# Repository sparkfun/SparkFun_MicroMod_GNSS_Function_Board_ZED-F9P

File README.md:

SparkFun MicroMod GNSS Function Board - ZED-F9P
========================================

[*SparkFun MicroMod GNSS Function Board - ZED-F9P (GPS-19663)*](https://www.sparkfun.com/products/19663)

The SparkFun MicroMod GNSS Function Board - ZED-F9P provides high precision GNSS capabilities for MicroMod projects using Main Board/Function Board assemblies. The ZED-F9P module from u-blox is capable of up to 10mm 3-dimensional accuracy though the module requires a clear view of the sky as well as correction data from an RTCM source to achieve this level of precision. The ZED-F9P can act as a base station as well so you can use it with a second Function Board (or another SparkFun ZED-F9P product) together to achieve millimeter positional accuracy.

Repository Contents
-------------------

* **/Documentation** - Data sheets, additional product information
* **/Firmware** - Example code 
* **/Hardware** - Eagle design files (.brd, .sch)
* **/Libraries** - Libraries for use with the <PRODUCT NAME>
* **/Production** - Production panel files (.brd)
* **/Software** - Related software for the <PRODUCT NAME>

Documentation
--------------
* **[SparkFun u-blox GNSS Arduino Library](https://github.com/sparkfun/SparkFun_u-blox_GNSS_Arduino_Library)** - u-blox GNSS Arduino library for SparkFun u-blox products.
* **[Hookup Guide](https://learn.sparkfun.com/tutorials/micromod-gnss-function-board---zed-f9p-hookup-guide)** - Basic hookup guide for the MicroMod GNSS Function Board - ZED-F9P.

Product Versions
----------------
* [GPS-19663](https://www.sparkfun.com/products/19663)- MicroMod GNSS Function Board - ZED-F9P Initial Release

Issues
------------
See the [issue template](.github/ISSUE_TEMPLATE/) folder for more information on how to raise issues for bugs and new features.

License Information
-------------------

This product is _**open source**_! 

Please review the LICENSE.md file for license information. 

If you have any questions or concerns on licensing, please contact technical support on our [SparkFun forums](https://forum.sparkfun.com/viewforum.php?f=152).

Distributed as-is; no warranty is given.

- Your friends at SparkFun.

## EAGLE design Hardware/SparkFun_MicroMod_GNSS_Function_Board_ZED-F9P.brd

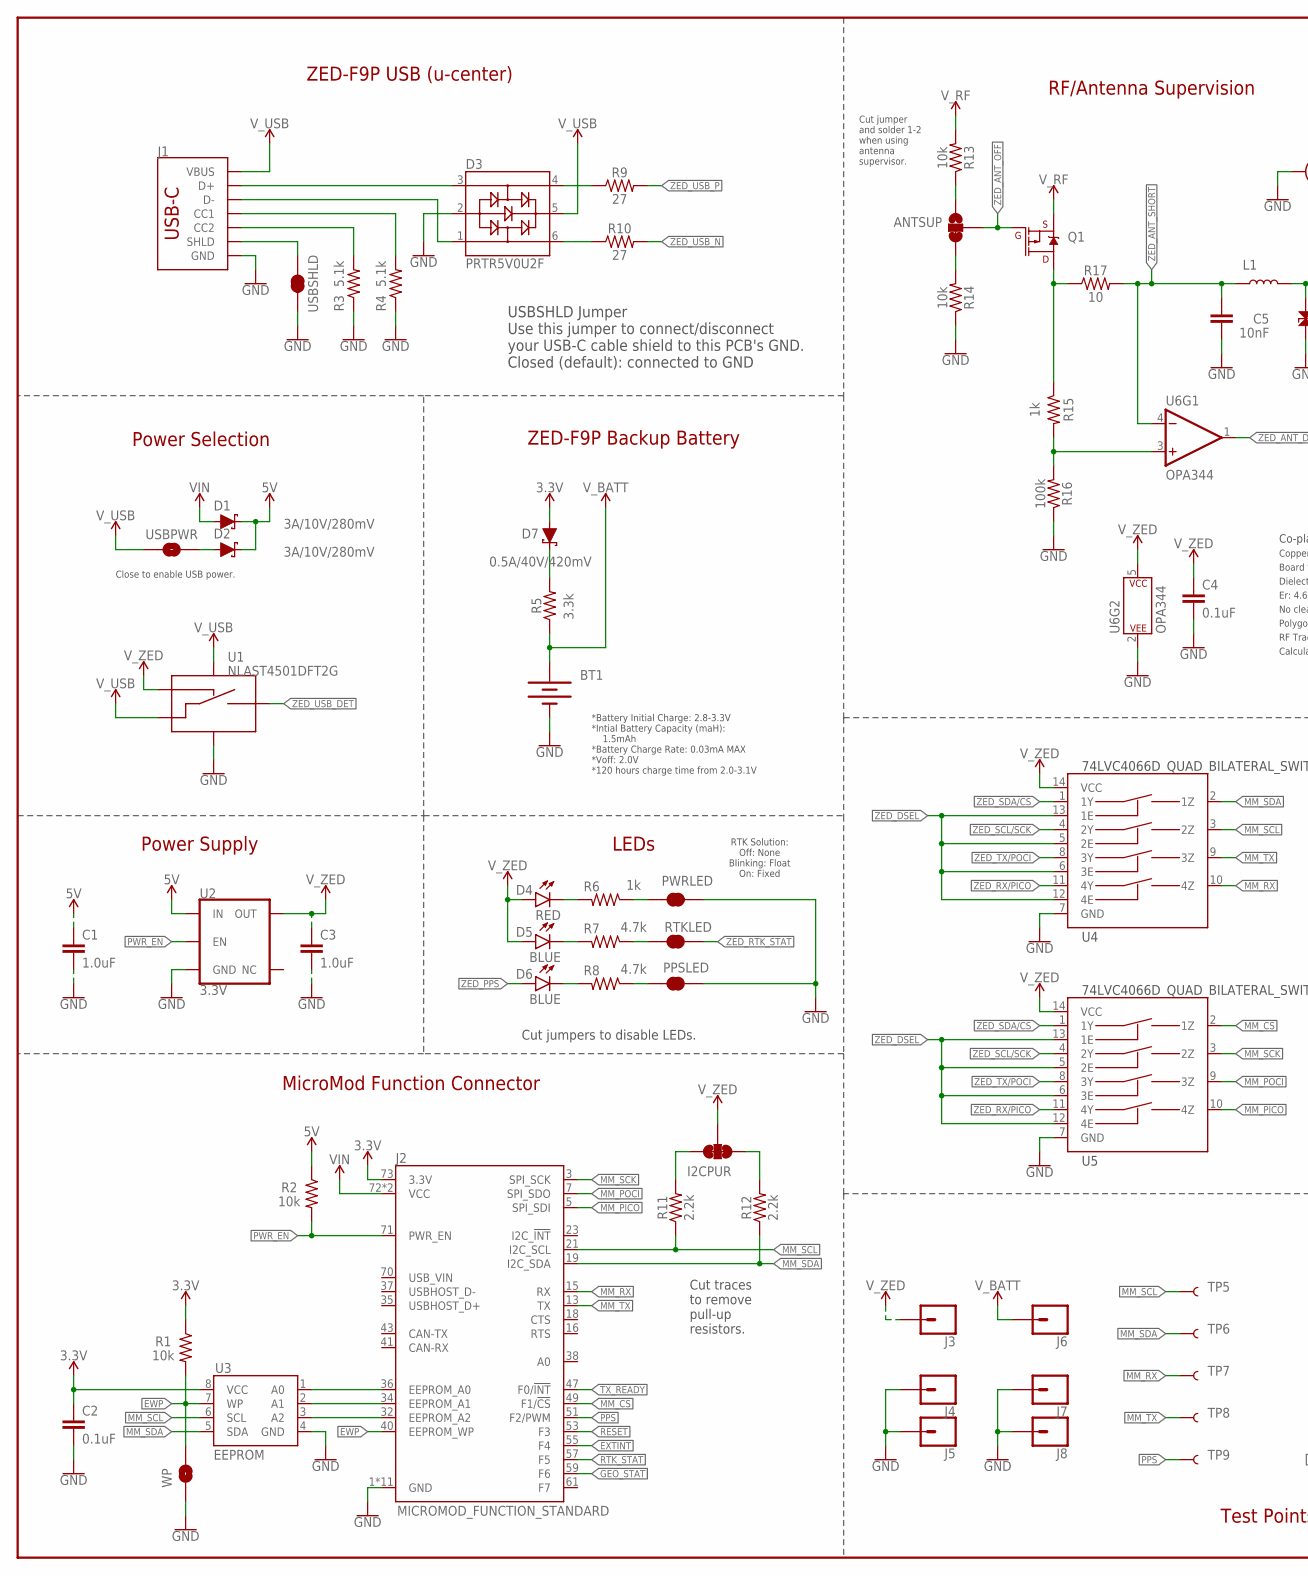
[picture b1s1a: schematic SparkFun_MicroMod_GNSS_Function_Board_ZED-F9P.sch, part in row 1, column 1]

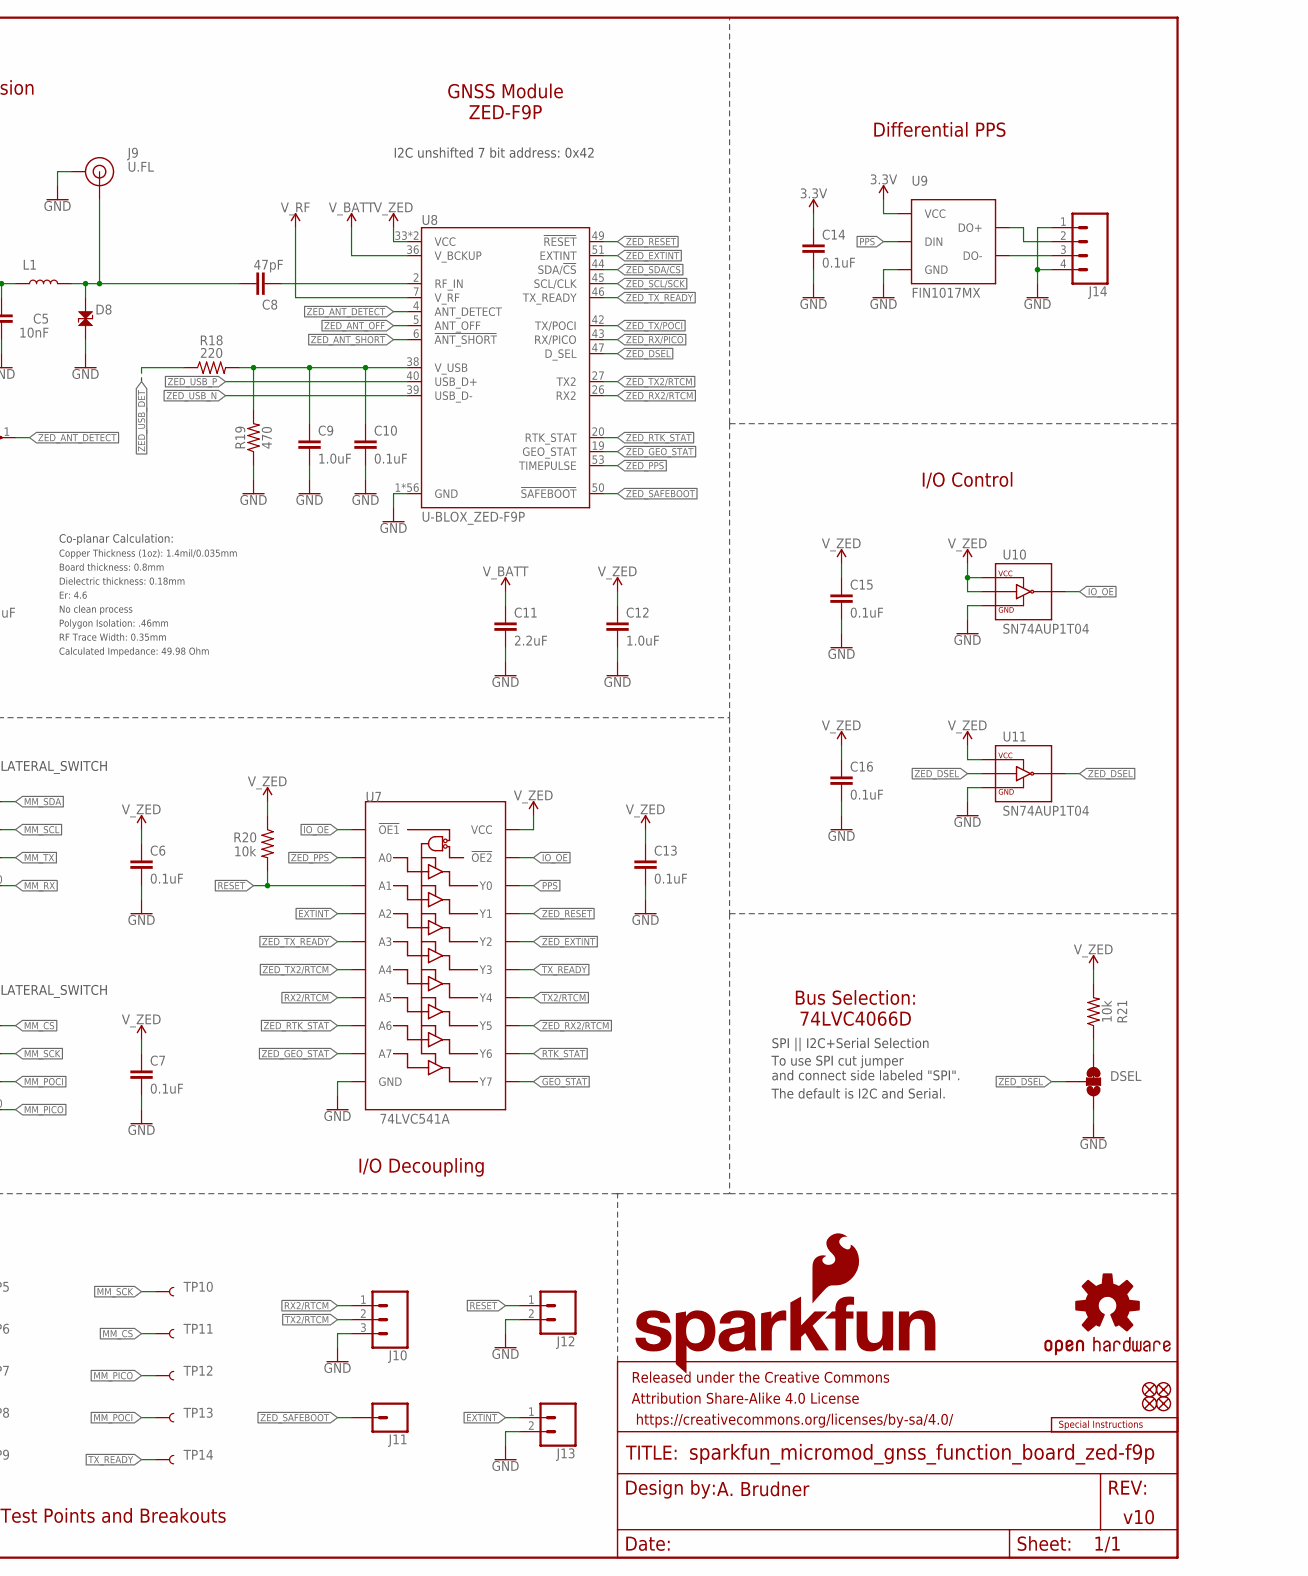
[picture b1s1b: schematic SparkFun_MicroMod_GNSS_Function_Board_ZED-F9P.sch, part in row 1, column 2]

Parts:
ANTSUP: JUMPER-SMT_3_1-NC_TRACE_SILK; SMT-JUMPER_3_1-NC_TRACE_SILK
BT1: RELOWABLE_BATTERY_MS421R; MS421R_IV03E
C1, C3, C9, C12: 1.0uF; 0402-TIGHT
C2, C4, C6, C7, C10, C13, C14, C15, C16: 0.1uF; 0402-TIGHT
C5: 10nF; 0402-TIGHT
C8: 47pF; 0402-TIGHT
C11: 2.2uF; 0402-TIGHT
D1, D2: 3A/10V/280mV; SOD-323
D3: PRTR5V0U2F; SOT886
D4: RED; LED-0603
D5, D6: BLUE; LED-0603
D7: 0.5A/40V/420mV; SOD-323
D8: PESD0402-0402T; 0402-TIGHT
DSEL: JUMPER-SMT_3_1-NC_TRACE_SILK; SMT-JUMPER_3_1-NC_TRACE_SILK
FD1, FD2, FD3, FD4: FIDUCIALUFIDUCIAL; FIDUCIAL-MICRO
FRAME1: FRAME-LEDGER; CREATIVE_COMMONS
I2CPUR: JUMPER-SMT_3_2-NC_TRACE_SILK; SMT-JUMPER_3_2-NC_TRACE_SILK
J1: USB Female Type C Connector; USB-C-16P-4LAYER-ISOLATED
J2: MICROMOD_FUNCTION_STANDARD; M.2-CARD-E-22_FUNCTION_STANDARD
J3, J4, J5, J7, J8, J11: CONN_01PTH_NO_SILK_YES_STOP; 1X01_NO_SILK
J6: CONN_01PTH_NO_SILK_SMALL; 1X01_SMALL
J9: U.FL
J10: 455-1750-1-ND; 1X03_NO_SILK
J12, J13: CONN_021X02_NO_SILK; 1X02_NO_SILK
J14: CONN_041X04_NO_SILK; 1X04_NO_SILK
L1: 150nH; 0402_MURATA
LOGO1: SFE_LOGO_NAME_FLAMEBLANK; BLANK
LOGO2: SPECIAL_INSTRUCTIONS-ORDERING; ORDERING_INSTRUCTIONS
LOGO3: OSHW-LOGOMINI; OSHW-LOGO-MINI
PPSLED: JUMPER-SMT_2_NC_TRACE_SILK; SMT-JUMPER_2_NC_TRACE_SILK
PWRLED: JUMPER-SMT_2_NC_TRACE_SILK; SMT-JUMPER_2_NC_TRACE_SILK
Q1: DMP21D0UT-7; SOT523
R1, R2, R13, R14, R20, R21: 10k; 0402-TIGHT
R3, R4: 5.1k; 0402-TIGHT
R5: 3.3K; 0402-TIGHT
R6, R15: 1k; 0402-TIGHT
R7, R8: 4.7k; 0402-TIGHT
R9, R10: 27; 0402-TIGHT
R11, R12: 2.2k; 0402-TIGHT
R16: 100k; 0402-TIGHT
R17: 10; 0603
R18: 220; 0402-TIGHT
R19: 470; 0402-TIGHT
RTKLED: JUMPER-SMT_2_NC_TRACE_SILK; SMT-JUMPER_2_NC_TRACE_SILK
TP5, TP6, TP7, TP8, TP9, TP10, TP11, TP12, TP13, TP14: TEST-POINT3; PAD.03X.03
U1: NLAST4501DFT2G; SOT353
U2: 3.3V; SOT23-5
U3: EEPROM; SO08
U4, U5: 74LVC4066D_QUAD_BILATERAL_SWITCH; SO14
U6: OPA344; SOT23-5
U7: 74LVC541A; DHVQFN20
U8: U-BLOX_ZED-F9P; ZED-F9P
U9: FIN1017MX; SO08
U10, U11: SN74AUP1T04; SC-70-5_DCK
USBPWR: JUMPER-SMT_2_NO_SILK; SMT-JUMPER_2_NO_SILK
USBSHLD: JUMPER-SMT_2_NC_TRACE_SILK; SMT-JUMPER_2_NC_TRACE_SILK
WP: JUMPER-SMT_2_NO_SILK; SMT-JUMPER_2_NO_SILK

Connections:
3.3V: C2.1, C14.1, D7.A, J2.73 (3.3V), R1.1, U3.8 (VCC), U9.1 (VCC)
5V: C1.1, D1.C, D2.C, R2.1, U2.1 (IN)
!RESET!: J2.53 (F3), J12.1, R20.2, U7.3 (A1)
!ZED_DSEL!: U5.5 (2E), U5.6 (3E), U5.12 (4E), U5.13 (1E), U11.4 (Y)
A0: J2.36 (EEPROM_A0), U3.1 (A0)
A1: J2.34 (EEPROM_A1), U3.2 (A1)
A2: J2.32 (EEPROM_A2), U3.3 (A2)
EWP: J2.40 (EEPROM_WP), R1.2, U3.7 (WP), WP.2
EXTINT: J2.55 (F4), J13.1, U7.4 (A2)
GEO_STAT: J2.59 (F6), U7.11 (Y7)
GND: BT1.-, C1.2, C2.2, C3.2, C4.2, C5.2, C6.2, C7.2, C9.2, C10.2, C11.2, C12.2, C13.2, C14.2, C15.2, C16.2, D3.2, D8.2, DSEL.1, J1.GND, J1.GND2 (GND), J2.1 (GND), J2.33 (GND), J2.39 (GND), J2.45 (GND), J2.75 (GND), J2.GND1 (GND), J2.GND2 (GND), J2.GND3 (GND), J2.GND4 (GND), J2.GND5 (GND), J2.GND6 (GND), J4.1, J5.1, J7.1, J8.1, J9.1 (GND), J9.2 (GND), J10.3, J12.2, J13.2, J14.1, J14.4, PPSLED.1, PWRLED.2, R3.1, R4.1, R14.1, R16.1, R19.1, U1.3 (GND), U2.2 (GND), U3.4 (GND), U4.7 (GND), U5.7 (GND), U6.2 (P$V-), U7.10 (GND), U7.EPAD (GND), U8.1 (GND), U8.3 (GND), U8.12 (GND), U8.14 (GND), U8.32 (GND), U8.37 (GND), U8.41 (GND), U8.48 (GND), U8.55 (GND), U8.56 (GND), U8.57 (GND), U8.58 (GND), U8.59 (GND), U8.60 (GND), U8.61 (GND), U8.62 (GND), U8.63 (GND), U8.64 (GND), U8.65 (GND), U8.66 (GND), U8.67 (GND), U8.68 (GND), U8.69 (GND), U8.70 (GND), U8.71 (GND), U8.72 (GND), U8.73 (GND), U8.74 (GND), U8.75 (GND), U8.76 (GND), U8.77 (GND), U8.78 (GND), U8.79 (GND), U8.80 (GND), U8.81 (GND), U8.82 (GND), U8.83 (GND), U8.84 (GND), U8.85 (GND), U8.86 (GND), U8.87 (GND), U8.88 (GND), U8.89 (GND), U8.90 (GND), U8.91 (GND), U8.92 (GND), U8.93 (GND), U8.94 (GND), U8.95 (GND), U8.96 (GND), U8.97 (GND), U8.98 (GND)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
IO_!OE!: U7.1 (!OE1!), U7.19 (!OE2!), U10.4 (Y)
MM_!CS!: J2.49 (F1/!CS!), TP11.1, U5.2 (1Z)
MM_PICO: J2.5 (SPI_SDI), TP12.1, U5.10 (4Z)
MM_POCI: J2.7 (SPI_SDO), TP13.1, U5.9 (3Z)
MM_RX: J2.15 (RX), TP7.1, U4.10 (4Z)
MM_SCK: J2.3 (SPI_SCK), TP10.1, U5.3 (2Z)
MM_SCL: J2.21 (I2C_SCL), R11.1, TP5.1, U3.6 (SCL), U4.3 (2Z)
MM_SDA: J2.19 (I2C_SDA), R12.1, TP6.1, U3.5 (SDA), U4.2 (1Z)
MM_TX: J2.13 (TX), TP8.1, U4.9 (3Z)
unnamed: ANTSUP.1, R13.1
unnamed: ANTSUP.3, R14.2
unnamed: J1.B5 (CC2), R3.2
unnamed: J1.A5 (CC1), R4.2
unnamed: DSEL.3, R21.1
unnamed: I2CPUR.3, R11.2
unnamed: C8.1, D8.1, J9.FEED (SIGNAL), L1.2
unnamed: R7.1, RTKLED.2
unnamed: I2CPUR.1, R12.2
unnamed: Q1.1 (D), R15.1, R17.1
unnamed: C9.1, C10.1, R18.2, R19.2, U8.38 (V_USB)
unnamed: D2.A, USBPWR.2
unnamed: PWRLED.1, R6.1
unnamed: PPSLED.2, R8.1
unnamed: D6.C, R8.2
unnamed: D5.C, R7.2
unnamed: D4.C, R6.2
unnamed: D7.C, R5.2
unnamed: R15.2, R16.2, U6.3 (+IN)
PPS: J2.51 (F2/PWM), TP9.1, U7.18 (Y0), U9.2 (DIN)
PPS_DIFF_N: J14.3, U9.8 (DO-)
PPS_DIFF_P: J14.2, U9.7 (DO+)
PWR_EN: J2.71 (PWR_EN), R2.2, U2.3 (EN)
RF_IN: C8.2, U8.2 (RF_IN)
RTK_STAT: J2.57 (F5), U7.12 (Y6)
RX2/RTCM: J10.1, U7.7 (A5)
SHLD: J1.SHLD1 (SHLD), J1.SHLD2 (SHLD), J1.SHLD3 (SHLD), J1.SHLD4 (SHLD), J1.SHLD5 (SHLD), J1.SHLD6 (SHLD), J1.SHLD7 (SHLD), J1.SHLD8 (SHLD), USBSHLD.1
TX2/RTCM: J10.2, U7.14 (Y4)
TX_READY: J2.47 (F0/!INT!), TP14.1, U7.15 (Y3)
USBC_N: D3.1, J1.A7 (D-), J1.B7 (D-)
USBC_P: D3.3, J1.A6 (D+), J1.B6 (D+)
USB_N: D3.6, R10.1
USB_P: D3.4, R9.1
VIN: D1.A, J2.72 (VCC), J2.74 (VCC)
V_BATT: BT1.+, C11.1, J6.P$1, R5.1, U8.36 (V_BCKUP)
V_RF: Q1.2 (S), R13.2, U8.7 (V_RF)
V_USB: D3.5, J1.VBUS1 (VBUS), J1.VBUS2 (VBUS), U1.1 (COM), U1.5 (VCC), USBPWR.1
V_ZED: C3.1, C4.1, C6.1, C7.1, C12.1, C13.1, C15.1, C16.1, D4.A, D5.A, I2CPUR.2, J3.1, R20.1, R21.2, U1.4 (EN), U2.5 (OUT), U4.14 (VCC), U5.14 (VCC), U6.5 (P$V+), U7.20 (VCC), U8.33 (VCC), U8.34 (VCC), U10.2 (A), U10.5 (VCC), U11.5 (VCC)
ZED_!RESET!: U7.17 (Y1), U8.49 (!RESET!)
ZED_!SAFEBOOT!: J11.1, U8.50 (!SAFEBOOT!)
ZED_ANT_!SHORT!: C5.1, L1.1, R17.2, U6.4 (-IN), U8.6 (!ANT_SHORT!)
ZED_ANT_DETECT: U6.1 (OUT), U8.4 (ANT_DETECT)
ZED_ANT_OFF: ANTSUP.2, Q1.3 (G), U8.5 (ANT_OFF)
ZED_DSEL: DSEL.2, U4.5 (2E), U4.6 (3E), U4.12 (4E), U4.13 (1E), U8.47 (D_SEL), U11.2 (A)
ZED_EXTINT: U7.16 (Y2), U8.51 (EXTINT)
ZED_GEO_STAT: U7.9 (A7), U8.19 (GEO_STAT)
ZED_PPS: D6.A, U7.2 (A0), U8.53 (TIMEPULSE)
ZED_RTK_STAT: RTKLED.1, U7.8 (A6), U8.20 (RTK_STAT)
ZED_RX2/RTCM: U7.13 (Y5), U8.26 (RX2)
ZED_RX/PICO: U4.11 (4Y), U5.11 (4Y), U8.43 (RX/PICO)
ZED_SCL/SCK: U4.4 (2Y), U5.4 (2Y), U8.45 (SCL/CLK)
ZED_SDA/!CS!: U4.1 (1Y), U5.1 (1Y), U8.44 (SDA/!CS!)
ZED_TX2/RTCM: U7.6 (A4), U8.27 (TX2)
ZED_TX/POCI: U4.8 (3Y), U5.8 (3Y), U8.42 (TX/POCI)
ZED_TX_READY: U7.5 (A3), U8.46 (TX_READY)
ZED_USB_DET: R18.1, U1.2 (NO)
ZED_USB_N: R10.2, U8.39 (USB_D-)
ZED_USB_P: R9.2, U8.40 (USB_D+)

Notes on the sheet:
MicroMod Function Connector
A. Brudner
v10
ZED-F9P USB (u-center)
ZED-F9P Backup Battery
LEDs
Cut jumpers to disable LEDs.
I/O Decoupling
I/O Control
Power Supply
Power Selection
Board thickness: 0.8mm
Er: 4.6
Copper Thickness (1oz): 1.4mil/0.035mm
RF Trace Width: 0.35mm
Polygon Isolation: .46mm
No clean process
Dielectric thickness: 0.18mm
Co-planar Calculation:
Calculated Impedance: 49.98 Ohm
*Battery Initial Charge: 2.8-3.3V *Intial Battery Capacity (maH): 1.5mAh *Battery Charge Rate: 0.03mA MAX *Voff: 2.0V *120 hours charge time from 2.0-3.1V
GNSS Module ZED-F9P
RF/Antenna Supervision
Cut jumper and solder 1-2 when using antenna supervisor.
Differential PPS
Bus Selection: 74LVC4066D
To use SPI cut jumper and connect side labeled "SPI".
SPI || I2C+Serial Selection
The default is I2C and Serial.
Close to enable USB power.
Test Points and Breakouts
I2C unshifted 7 bit address: 0x42
Cut traces to remove pull-up resistors.
RTK Solution: Off: None Blinking: Float On: Fixed
USBSHLD Jumper Use this jumper to connect/disconnect your USB-C cable shield to this PCB's GND. Closed (default): connected to GND

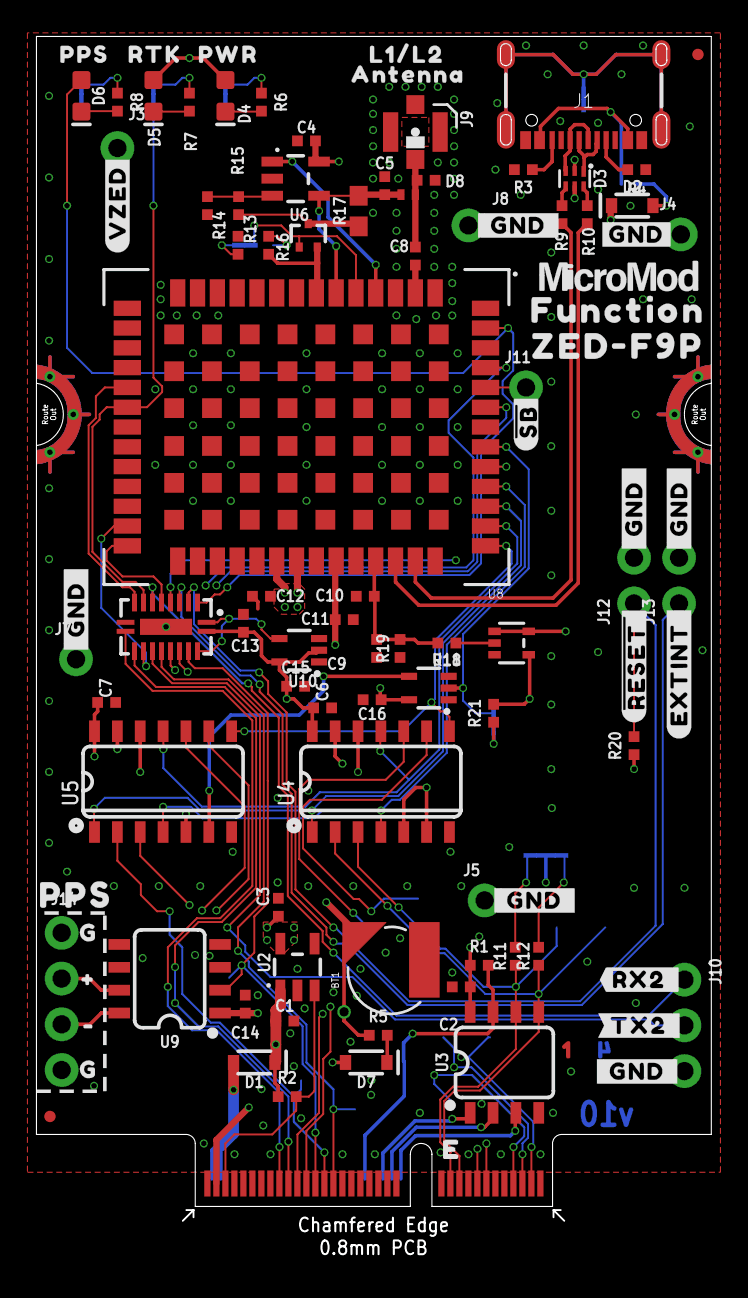
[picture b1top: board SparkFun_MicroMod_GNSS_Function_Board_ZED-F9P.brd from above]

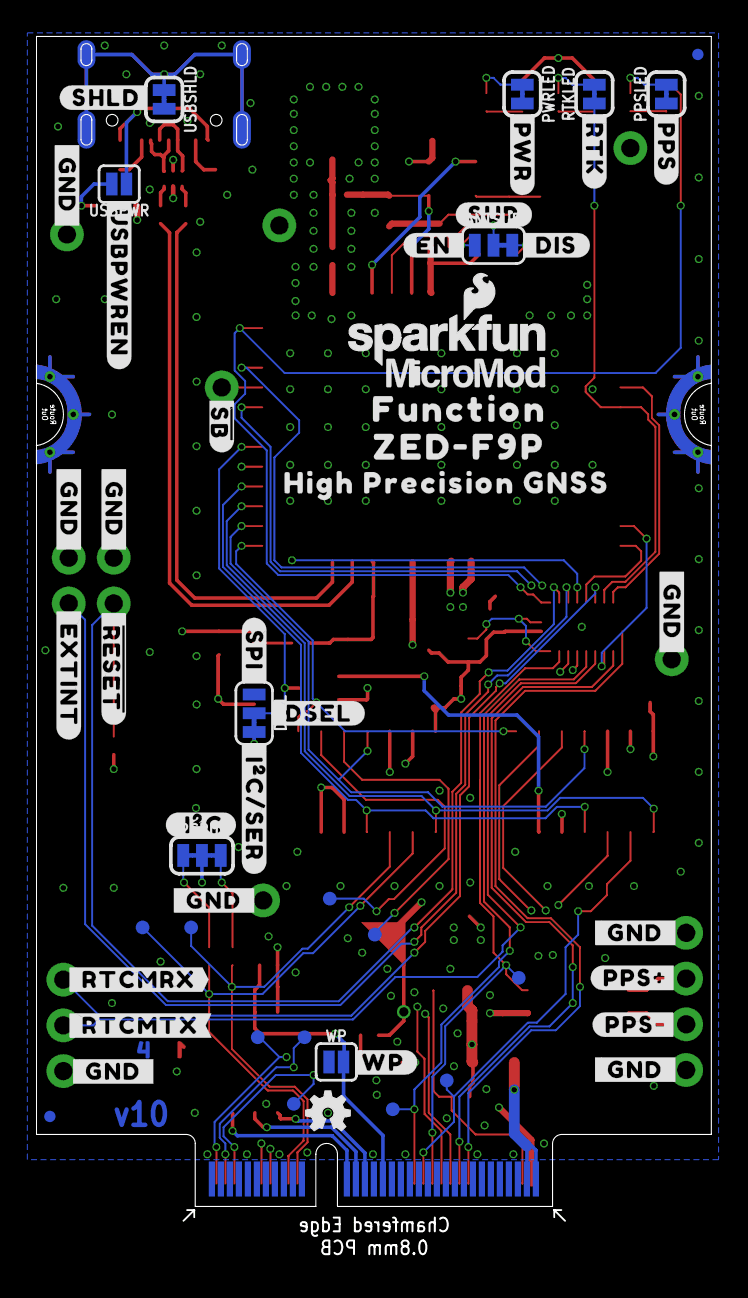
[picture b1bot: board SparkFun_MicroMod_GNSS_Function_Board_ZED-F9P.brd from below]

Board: 4 copper layers, 37.5 x 65.8 mm, 164 parts (56 on the bottom side), 78 nets.

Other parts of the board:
LOGO4: SFE_LOGO_NAME_FLAME.1_INCH; SFE_LOGO_NAME_FLAME_.1
U$1: 40
U$2: #_RTCMTX#0
U$3: #TX2_#0
U$5, U$6, U$7, U$9, U$10, U$11, U$18, U$19, U$21, U$22, U$25, U$33, U$38, U$39: #_GND_#0
U$12: #_RTCMRX#0
U$13: #RX2_#0
U$14: ##RESET_##0
U$15: #_#RESET##0
U$16: #_EXTINT#0
U$17: #EXTINT_#0
U$23: #_I�C#SER#0
U$24: #SPI_#0
U$26, U$27: FUNCTION0
U$28: #_I�C#0
U$29: #_DSEL#0
U$30: #SUP#0
U$31: #RTK#0
U$32: #PWR#0
U$34: 10
U$35: 211
U$36: 3212
U$37, U$63: MICROMOD_LOGO_.35
U$40: PPS3
U$44: #PPS##2252
U$45: #PPS##2253
U$46, U$47: G2
U$48: #3
U$49: #4
U$50: #PPS#2254
U$51: PPS0
U$52: RTK0
U$54: #WP#0
U$62: #USBPWREN#10
U$64: #SHLD#12
U$68: #VZED#0
U$72: PWR0
U$73: #_DIS#0
U$74: #EN_#0
U$76: ##SB##9
U$80: ##SB##0
U$82: #GND#0
U$85: L1#L20
U$87: ANTENNA0
U$104: SFE_LOGO_FLAME_STOP_.1
U$106: HIGH_PRECISION_GNSS26
U$112, U$114: ZED#F9P0

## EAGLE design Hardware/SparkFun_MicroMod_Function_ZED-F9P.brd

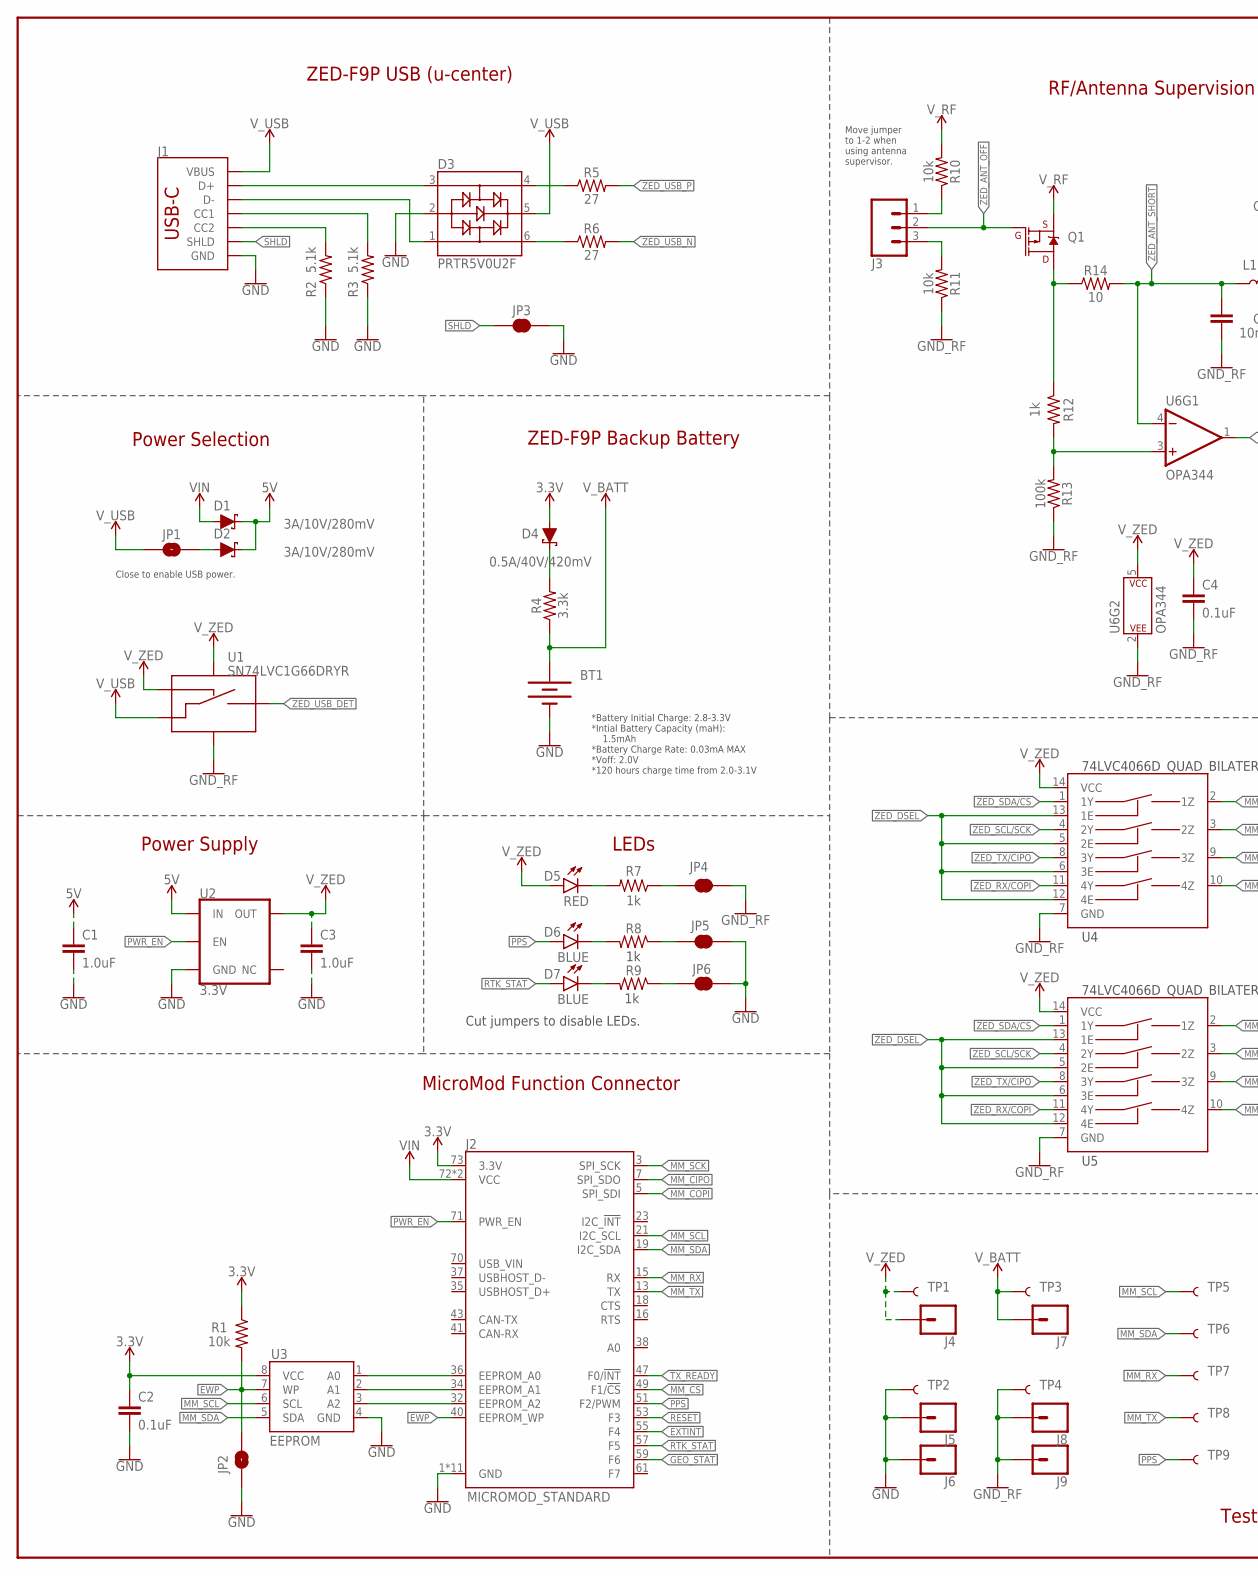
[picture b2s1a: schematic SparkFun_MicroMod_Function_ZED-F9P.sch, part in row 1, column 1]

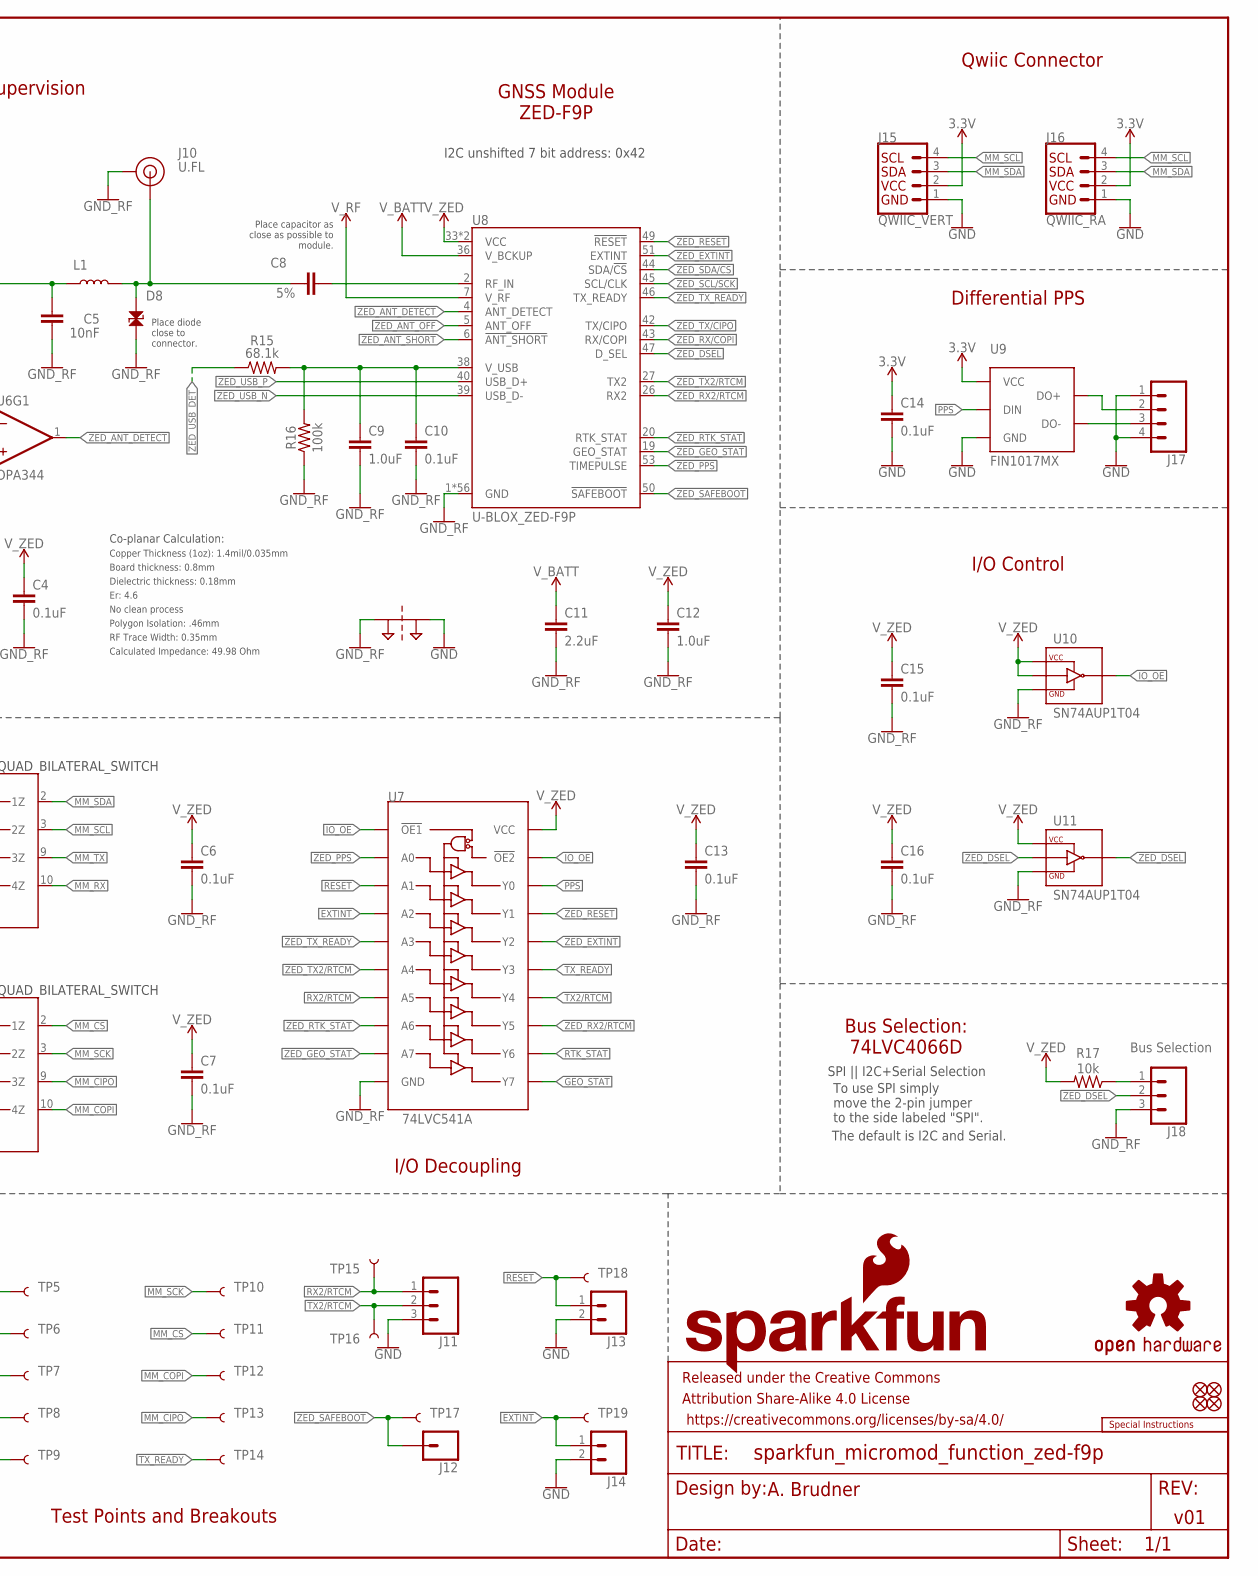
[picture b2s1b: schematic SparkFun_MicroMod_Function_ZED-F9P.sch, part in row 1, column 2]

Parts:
BT1: RELOWABLE_BATTERY_MS421R; MS421R_IV03E
C1, C3, C9, C12: 1.0uF; 0402-TIGHT
C2, C4, C6, C7, C10, C13, C14, C15, C16: 0.1uF; 0402-TIGHT
C5: 10nF; 0402-TIGHT
C8: 47pF; 0402-TIGHT
C11: 2.2uF; 0402-TIGHT
D1, D2: 3A/10V/280mV; SOD-323
D3: PRTR5V0U2F; SOT886
D4: 0.5A/40V/420mV; SOD-323
D5: RED; LED-0603
D6, D7: BLUE; LED-0603
D8: PESD0402-0402T; 0402-TIGHT
FD1, FD2, FD3, FD4: FIDUCIALUFIDUCIAL; FIDUCIAL-MICRO
FRAME1: FRAME-LEDGER; CREATIVE_COMMONS
J1: USB Female Type C Connector; USB-C-16P-4LAYER-ISOLATED
J2: MICROMOD_STANDARD; M.2-CARD-E-22_FUNCTION_STANDARD
J3, J18: Bus Selection; 1X03_LOCK
J4, J5, J6, J8, J9, J12: CONN_01; 1X01
J7: CONN_01PTH_NO_SILK_SMALL; 1X01_SMALL
J10: U.FL
J11: 455-1750-1-ND; 1X03
J13, J14: CONN_02; 1X02
J15: QWIIC_VERT; JST04_1MM_VERT
J16: QWIIC_RA; JST04_1MM_RA
J17: CONN_04PTH; 1X04
JP1, JP2: JUMPER-SMT_2_NO_SILK; SMT-JUMPER_2_NO_SILK
JP3, JP4, JP5, JP6: JUMPER-SMT_2_NC_TRACE_SILK; SMT-JUMPER_2_NC_TRACE_SILK
L1: 150nH; 0402_MURATA
LOGO1: SFE_LOGO_NAME_FLAMEBLANK; BLANK
LOGO2: SPECIAL_INSTRUCTIONS-ORDERING; ORDERING_INSTRUCTIONS
LOGO3: OSHW-LOGOMINI; OSHW-LOGO-MINI
Q1: DMP21D0UT-7; SOT523
R1, R10, R11, R17: 10k; 0603
R2, R3: 5.1k; 0603
R4: 3.3k; 0603
R5, R6: 27; 0402-TIGHT
R7, R8, R9, R12: 1k; 0603
R13, R16: 100k; 0603
R14: 10; 0603
R15: 68.1k; 0603
SUPPLYTIE1: 2PT_GND_TIE
TP1, TP2, TP3, TP4, TP5, TP6, TP7, TP8, TP9, TP10, TP11, TP12, TP13, TP14, TP15, TP16, TP17, TP18, TP19: TEST-POINT3; PAD.03X.03
U1: SN74LVC1G66DRYR; USON_DRY0006A
U2: 3.3V; SOT23-5
U3: EEPROM; SO08
U4, U5: 74LVC4066D_QUAD_BILATERAL_SWITCH; SO14
U6: OPA344; SOT23-5
U7: 74LVC541A; DHVQFN20
U8: U-BLOX_ZED-F9P; ZED-F9P
U9: FIN1017MX; SO08
U10, U11: SN74AUP1T04; SC-70-5_DCK

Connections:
3.3V: C2.1, C14.1, D4.A, J2.73 (3.3V), J15.2, J16.2, R1.1, U3.8 (VCC), U9.1 (VCC)
5V: C1.1, D1.C, D2.C, U2.1 (IN)
!RESET!: J2.53 (F3), J13.1, TP18.1, U7.P$3 (A1)
!ZED_DSEL!: U5.5 (2E), U5.6 (3E), U5.12 (4E), U5.13 (1E), U11.P$4 (Y)
A0: J2.36 (EEPROM_A0), U3.1 (A0)
A1: J2.34 (EEPROM_A1), U3.2 (A1)
A2: J2.32 (EEPROM_A2), U3.3 (A2)
EWP: J2.40 (EEPROM_WP), JP2.2, R1.2, U3.7 (WP)
EXTINT: J2.55 (F4), J14.1, TP19.1, U7.P$4 (A2)
GEO_STAT: J2.59 (F6), U7.P$11 (Y7)
GND: BT1.-, C1.2, C2.2, C3.2, C14.2, D3.2, J1.GND, J1.GND2 (GND), J2.1 (GND), J2.33 (GND), J2.39 (GND), J2.45 (GND), J2.75 (GND), J2.GND1 (GND), J2.GND2 (GND), J2.GND3 (GND), J2.GND4 (GND), J2.GND5 (GND), J2.GND6 (GND), J5.1, J6.1, J11.3, J13.2, J14.2, J15.1, J16.1, J17.1, J17.4, JP2.1, JP3.2, JP5.1, JP6.1, R2.1, R3.1, SUPPLYTIE1.P$2, TP2.1, U2.2 (GND), U3.4 (GND), U9.4 (GND)
GND_RF: C4.2, C5.2, C6.2, C7.2, C9.2, C10.2, C11.2, C12.2, C13.2, C15.2, C16.2, D8.2, J8.1, J9.1, J10.1 (GND), J10.2 (GND), J18.3, JP4.2, R11.1, R13.1, R16.1, SUPPLYTIE1.P$1, TP4.1, U1.P$3 (VSS), U4.7 (GND), U5.7 (GND), U6.2 (P$V-), U7.EPAD (GND), U7.P$10 (GND), U8.1 (GND), U8.3 (GND), U8.12 (GND), U8.14 (GND), U8.32 (GND), U8.37 (GND), U8.41 (GND), U8.48 (GND), U8.55 (GND), U8.56 (GND), U8.57 (GND), U8.58 (GND), U8.59 (GND), U8.60 (GND), U8.61 (GND), U8.62 (GND), U8.63 (GND), U8.64 (GND), U8.65 (GND), U8.66 (GND), U8.67 (GND), U8.68 (GND), U8.69 (GND), U8.70 (GND), U8.71 (GND), U8.72 (GND), U8.73 (GND), U8.74 (GND), U8.75 (GND), U8.76 (GND), U8.77 (GND), U8.78 (GND), U8.79 (GND), U8.80 (GND), U8.81 (GND), U8.82 (GND), U8.83 (GND), U8.84 (GND), U8.85 (GND), U8.86 (GND), U8.87 (GND), U8.88 (GND), U8.89 (GND), U8.90 (GND), U8.91 (GND), U8.92 (GND), U8.93 (GND), U8.94 (GND), U8.95 (GND), U8.96 (GND), U8.97 (GND), U8.98 (GND), U8.99 (GND), U8.100 (GND), U8.101 (GND), U8.102 (GND), U10.P$3 (GND), U11.P$3 (GND)
IO_!OE!: U7.P$1 (!OE1!), U7.P$19 (!OE2!), U10.P$4 (Y)
MM_!CS!: J2.49 (F1/!CS!), TP11.1, U5.2 (1Z)
MM_CIPO: J2.7 (SPI_SDO), TP13.1, U5.9 (3Z)
MM_COPI: J2.5 (SPI_SDI), TP12.1, U5.10 (4Z)
MM_RX: J2.15 (RX), TP7.1, U4.10 (4Z)
MM_SCK: J2.3 (SPI_SCK), TP10.1, U5.3 (2Z)
MM_SCL: J2.21 (I2C_SCL), J15.4, J16.4, TP5.1, U3.6 (SCL), U4.3 (2Z)
MM_SDA: J2.19 (I2C_SDA), J15.3, J16.3, TP6.1, U3.5 (SDA), U4.2 (1Z)
MM_TX: J2.13 (TX), TP8.1, U4.9 (3Z)
unnamed: J1.B5 (CC2), R2.2
unnamed: J1.A5 (CC1), R3.2
unnamed: C8.1, D8.1, J10.FEED (SIGNAL), L1.P$2 (2)
unnamed: JP6.2, R9.1
unnamed: J18.1, R17.1
unnamed: J3.1, R10.1
unnamed: J3.3, R11.2
unnamed: Q1.P$1 (D), R12.1, R14.1
unnamed: C9.1, C10.1, R15.2, R16.2, U8.38 (V_USB)
unnamed: D2.A, JP1.2
unnamed: JP4.1, R7.1
unnamed: JP5.2, R8.1
unnamed: D6.C, R8.2
unnamed: D7.C, R9.2
unnamed: D5.C, R7.2
unnamed: D4.C, R4.2
unnamed: R12.2, R13.2, U6.3 (+IN)
PPS: D6.A, J2.51 (F2/PWM), TP9.1, U7.P$18 (Y0), U9.2 (DIN)
PPS_DIFF_N: J17.3, U9.8 (DO-)
PPS_DIFF_P: J17.2, U9.7 (DO+)
PWR_EN: J2.71 (PWR_EN), U2.3 (EN)
RF_IN: C8.2, U8.2 (RF_IN)
RTK_STAT: D7.A, J2.57 (F5), U7.P$12 (Y6)
RX2/RTCM: J11.1, TP15.1, U7.P$7 (A5)
SHLD: J1.SHLD1 (SHLD), J1.SHLD2 (SHLD), J1.SHLD3 (SHLD), J1.SHLD4 (SHLD), J1.SHLD5 (SHLD), J1.SHLD6 (SHLD), J1.SHLD7 (SHLD), J1.SHLD8 (SHLD), JP3.1
TX2/RTCM: J11.2, TP16.1, U7.P$14 (Y4)
TX_READY: J2.47 (F0/!INT!), TP14.1, U7.P$15 (Y3)
USBC_N: D3.1, J1.A7 (D-), J1.B7 (D-)
USBC_P: D3.3, J1.A6 (D+), J1.B6 (D+)
USB_N: D3.6, R6.1
USB_P: D3.4, R5.1
VIN: D1.A, J2.72 (VCC), J2.74 (VCC)
V_BATT: BT1.+, C11.1, J7.P$1, R4.1, TP3.1, U8.36 (V_BCKUP)
V_RF: Q1.P$2 (S), R10.2, U8.7 (V_RF)
V_USB: D3.5, J1.VBUS1 (VBUS), J1.VBUS2 (VBUS), JP1.1, U1.P$1 (A_IN)
V_ZED: C3.1, C4.1, C6.1, C7.1, C12.1, C13.1, C15.1, C16.1, D5.A, J4.1, R17.2, TP1.1, U1.P$4 (CTRL_IN), U1.P$6 (VCC), U2.5 (OUT), U4.14 (VCC), U5.14 (VCC), U6.5 (P$V+), U7.P$20 (VCC), U8.33 (VCC), U8.34 (VCC), U10.P$2 (A), U10.P$5 (VCC), U11.P$5 (VCC)
ZED_!RESET!: U7.P$17 (Y1), U8.49 (!RESET!)
ZED_!SAFEBOOT!: J12.1, TP17.1, U8.50 (!SAFEBOOT!)
ZED_ANT_!SHORT!: C5.1, L1.P$1 (1), R14.2, U6.4 (-IN), U8.6 (!ANT_SHORT!)
ZED_ANT_DETECT: U6.1 (OUT), U8.4 (ANT_DETECT)
ZED_ANT_OFF: J3.2, Q1.P$3 (G), U8.5 (ANT_OFF)
ZED_DSEL: J18.2, U4.5 (2E), U4.6 (3E), U4.12 (4E), U4.13 (1E), U8.47 (D_SEL), U11.P$2 (A)
ZED_EXTINT: U7.P$16 (Y2), U8.51 (EXTINT)
ZED_GEO_STAT: U7.P$9 (A7), U8.19 (GEO_STAT)
ZED_PPS: U7.P$2 (A0), U8.53 (TIMEPULSE)
ZED_RTK_STAT: U7.P$8 (A6), U8.20 (RTK_STAT)
ZED_RX2/RTCM: U7.P$13 (Y5), U8.26 (RX2)
ZED_RX/COPI: U4.11 (4Y), U5.11 (4Y), U8.43 (RX/COPI)
ZED_SCL/SCK: U4.4 (2Y), U5.4 (2Y), U8.45 (SCL/CLK)
ZED_SDA/!CS!: U4.1 (1Y), U5.1 (1Y), U8.44 (SDA/!CS!)
ZED_TX2/RTCM: U7.P$6 (A4), U8.27 (TX2)
ZED_TX/CIPO: U4.8 (3Y), U5.8 (3Y), U8.42 (TX/CIPO)
ZED_TX_READY: U7.P$5 (A3), U8.46 (TX_READY)
ZED_USB_DET: R15.1, U1.P$2 (A_OUT)
ZED_USB_N: R6.2, U8.39 (USB_D-)
ZED_USB_P: R5.2, U8.40 (USB_D+)

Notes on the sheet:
MicroMod Function Connector
A. Brudner
v01
ZED-F9P USB (u-center)
ZED-F9P Backup Battery
LEDs
Cut jumpers to disable LEDs.
Qwiic Connector
I/O Decoupling
I/O Control
Power Supply
Power Selection
Board thickness: 0.8mm
Er: 4.6
Copper Thickness (1oz): 1.4mil/0.035mm
RF Trace Width: 0.35mm
Polygon Isolation: .46mm
No clean process
Dielectric thickness: 0.18mm
Co-planar Calculation:
Calculated Impedance: 49.98 Ohm
*Battery Initial Charge: 2.8-3.3V *Intial Battery Capacity (maH): 1.5mAh *Battery Charge Rate: 0.03mA MAX *Voff: 2.0V *120 hours charge time from 2.0-3.1V
Place capacitor as close as possible to module.
GNSS Module ZED-F9P
RF/Antenna Supervision
Place diode close to connector.
Move jumper to 1-2 when using antenna supervisor.
Differential PPS
Bus Selection: 74LVC4066D
To use SPI simply move the 2-pin jumper to the side labeled "SPI".
SPI || I2C+Serial Selection
The default is I2C and Serial.
Close to enable USB power.
Test Points and Breakouts
I2C unshifted 7 bit address: 0x42

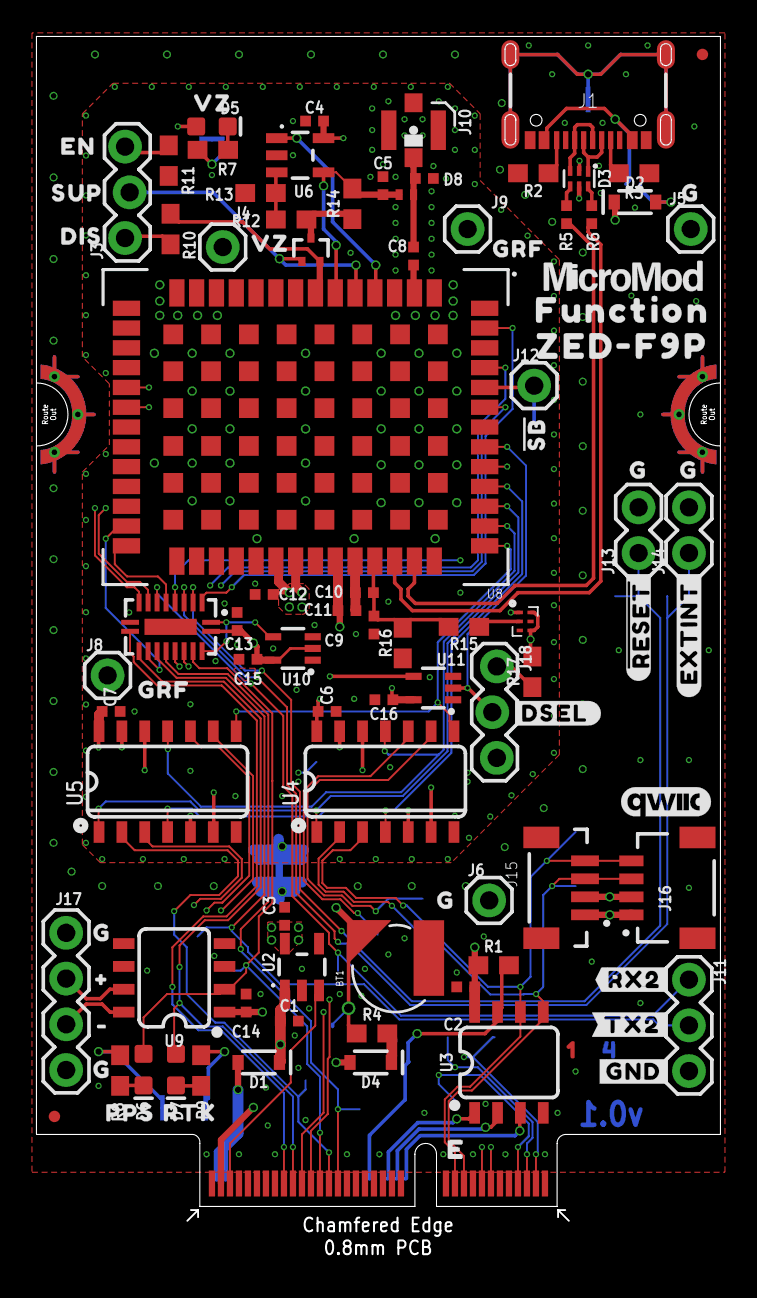
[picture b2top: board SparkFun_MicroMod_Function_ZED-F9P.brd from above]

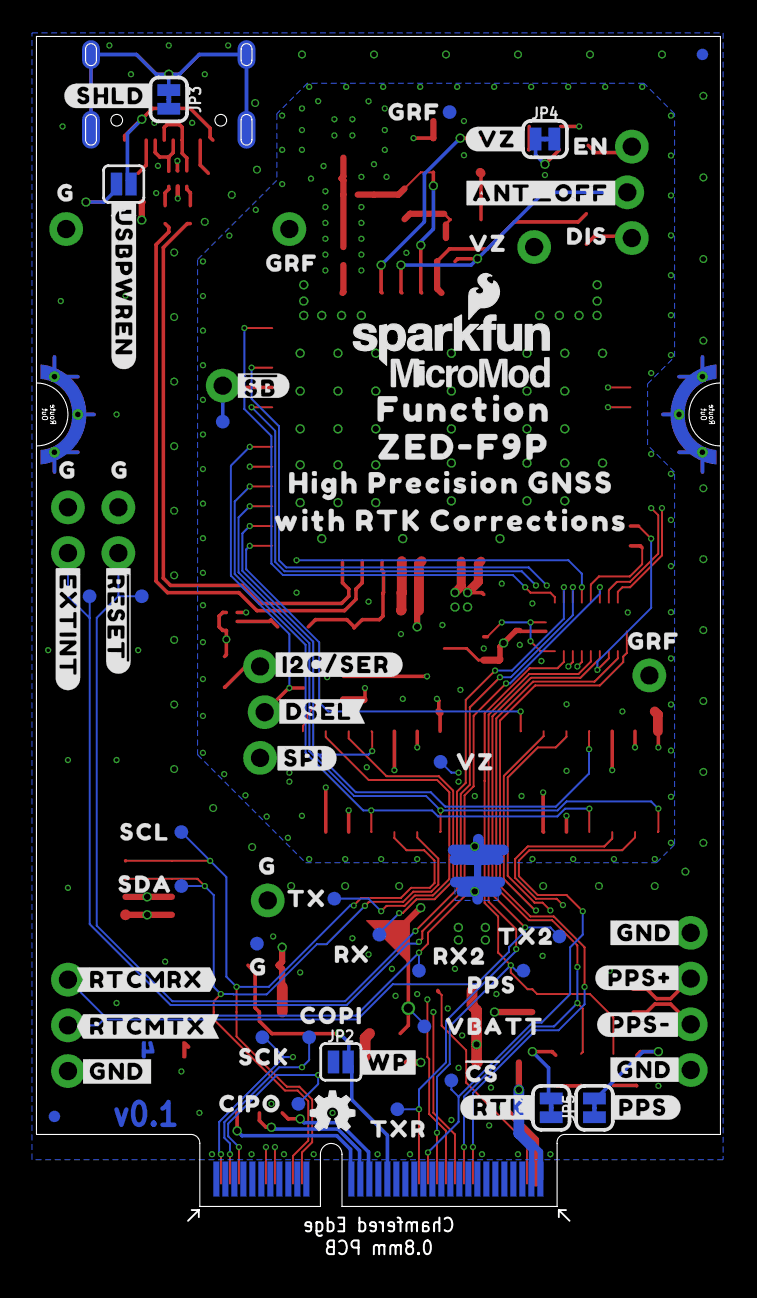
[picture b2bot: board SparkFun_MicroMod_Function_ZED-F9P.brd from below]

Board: 4 copper layers, 38.0 x 65.8 mm, 191 parts (80 on the bottom side), 77 nets.

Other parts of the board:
LOGO4: SFE_LOGO_NAME_FLAME.1_INCH; SFE_LOGO_NAME_FLAME_.1
U$26, U$27: FUNCTION0
U$34: 10
U$35: 211
U$36: 3212
U$37, U$63: MICROMOD_LOGO_.35
U$38: 43213
U$39: #RTCMTX#0
U$40: #RTCMRX#0
U$41, U$42, U$43, U$99: #GND#0
U$44: #PPS##2252
U$45: #PPS##2253
U$46, U$47, U$55, U$56, U$57, U$58, U$59, U$78, U$79, U$101, U$102: G2
U$48: #3
U$49: #4
U$50: #PPS#2254
U$51: PPS0
U$52: RTK0
U$53: #RTK#2255
U$54: #WP#8
U$60: #EXTINT#0
U$61: #EXTINT#2
U$62: #USBPWREN#10
U$64: #SHLD#12
U$65: ##RESET##3
U$66, U$67, U$69, U$96, U$100: GRF17
U$68: COPI2239
U$70: #SPI#30
U$71: VBATT18
U$72: VZ4
U$73, U$89, U$90: VZ19
U$74: #ANT_OFF#22
U$75: #VZ#5
U$76: ##SB##9
U$77: WITH_RTK_CORRECTIONS28
U$80: #SB#29
U$81: #DSEL#29
U$82: RX231
U$83: RX232
U$84: TX233
U$85: TX2234
U$86: PPS2235
U$87: SCL2236
U$88: SDA2237
U$91: CIPO2240
U$92: SCK2241
U$93: TXR2246
U$94: #CS#2245
U$95: #DSEL#31
U$97: #RX2#2249
U$98: #TX2#2249
U$103: #I2C#SER#30
U$104: SFE_LOGO_FLAME_STOP_.1
U$105: ##RESET##0
U$106: HIGH_PRECISION_GNSS26
U$107, U$110: EN32
U$108, U$109: DIS33
U$111: SUP35
U$112, U$114: ZED#F9P0
U$113: QWIIC_5MM

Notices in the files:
parts and their libraries:
SparkFun-Aesthetics: Licensing: Creative Commons ShareAlike 4.0 International - https://creativecommons.org/licenses/by-sa/4.0
SparkFun-Aesthetics: Released under the Creative Commons Attribution Share-Alike 4.0 License
SparkFun-Aesthetics: https://creativecommons.org/licenses/by-sa/4.0
